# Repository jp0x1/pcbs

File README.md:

# pcbs
The pcbs that I have made for personal projects, clubs, coursework, etc.

## mcp3008

My first pcb design. A semi-breakout board for the MCP3008 ADC I tried to design for an fpga audio acquisition project.
The layout is really bad, placing could definitely be better if needed, and it's extremely basic.

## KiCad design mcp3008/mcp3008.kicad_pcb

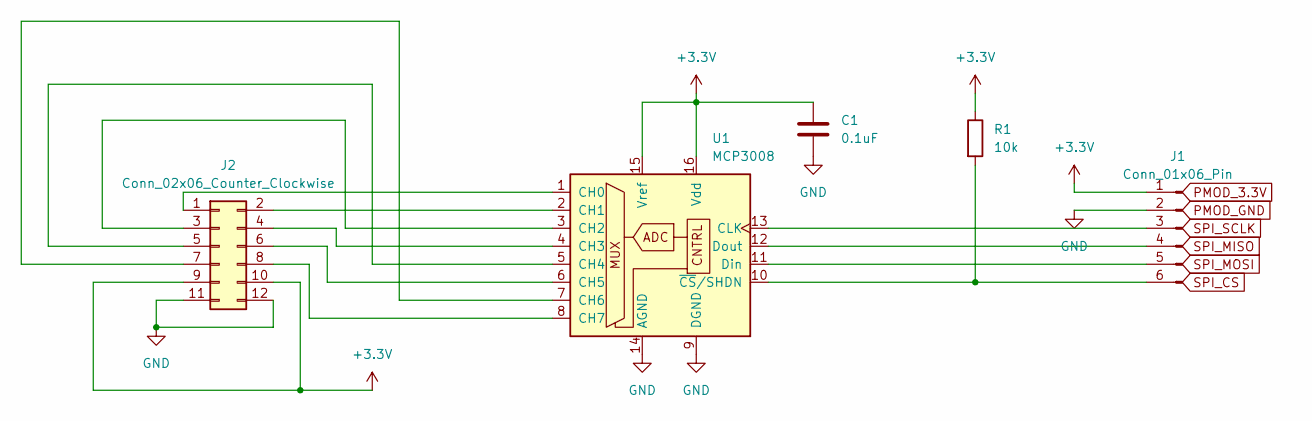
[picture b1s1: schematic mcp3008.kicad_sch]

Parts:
C1: 0.1uF; C_0603_1608Metric
J1: Conn_01x06_Pin; PinHeader_1x06_P2.54mm_Vertical
J2: Conn_02x06_Counter_Clockwise; PinHeader_2x06_P2.54mm_Vertical
R1: 10k; R_0603_1608Metric
U1: MCP3008; SOIC-16_3.9x9.9mm_P1.27mm

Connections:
+3.3V: C1.1, J1.1, J2.9, J2.10, R1.1, U1.15 (Vref), U1.16 (Vdd)
GND: C1.2, J1.2, J2.11, J2.12, U1.9 (DGND), U1.14 (AGND)
unnamed: J1.3, U1.13 (CLK)
unnamed: J1.4, U1.12 (Dout)
unnamed: J1.5, U1.11 (Din)
unnamed: J1.6, R1.2, U1.10 (~CS/SHDN)
unnamed: J2.1, U1.1 (CH0)
unnamed: J2.2, U1.2 (CH1)
unnamed: J2.3, U1.3 (CH2)
unnamed: J2.4, U1.4 (CH3)
unnamed: J2.5, U1.5 (CH4)
unnamed: J2.6, U1.6 (CH5)
unnamed: J2.7, U1.7 (CH6)
unnamed: J2.8, U1.8 (CH7)

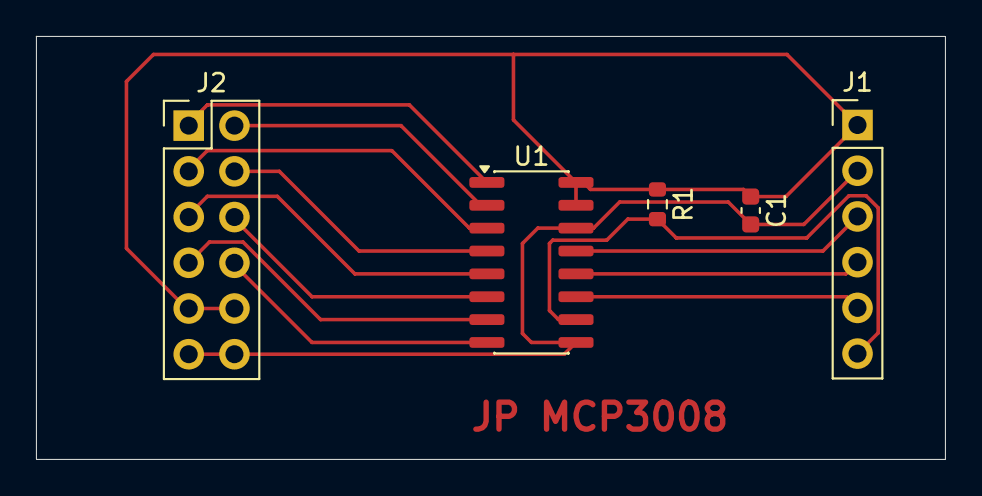
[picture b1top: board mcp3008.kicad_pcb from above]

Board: 2 copper layers, 50.5 x 23.5 mm, 5 parts (0 on the bottom side), 14 nets.

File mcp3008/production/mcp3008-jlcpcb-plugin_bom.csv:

Designator,Footprint,Quantity,Value,LCSC Part #
C1,0603,1,0.1uF,
J1,PinHeader_1x06_P2.54mm_Vertical,1,Conn_01x06_Pin,
J2,PinHeader_2x06_P2.54mm_Vertical,1,Conn_02x06_Counter_Clockwise,
R1,0603,1,10k,
U1,SOIC-16_3.9x9.9mm_P1.27mm,1,MCP3008,
